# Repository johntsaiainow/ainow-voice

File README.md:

# AI-Now Voice Hardware

Open-source PCB hardware repository for **AiNow Voice S3** — a family of ESP32-S3 based dual-microphone AI voice assistant cards.

> **Note:** This hardware is no longer tied to the "XiaoZhi" firmware. It is a general-purpose ESP32-S3 voice platform compatible with any ESP-SR / ESP-ADF / custom voice pipeline.

---

## 📂 Product Variations (directly under root)

| Variation | MCU | Mic | Display | Amp | Status | Folder |
| :--- | :--- | :--- | :--- | :--- | :--- | :--- |
| **AiNow Voice S3 — Standard** | ESP32-S3-WROOM-1-N16R8 | 2× I2S MEMS (INMP441/MSM261S socketed) | ST7789 1.54" TFT | MAX98357A | Released | [`s3-dualmic-standard`](./s3-dualmic-standard) |
| AiNow Voice S3 — Mini | ESP32-S3-WROOM-1-N8R8 | 2× I2S MEMS | None (LED status only) | MAX98357A | Planned | [`s3-dualmic-mini`](./s3-dualmic-mini) |
| AiNow Voice S3 — Pro | ESP32-S3-WROOM-1-N16R8 | ES7210 4-ch ADC + Analog MEMS | ST7789 + OLED | NS4168 + passive filter | In design | [`s3-dualmic-pro`](./s3-dualmic-pro) |

> Each sub-folder contains its own `README.md`, KiCad schematic/PCB files, Gerber output, and 3D model notes.

---

## 🚀 Quick Start

1. Enter the variation folder you want to build (e.g. `s3-dualmic-standard/`) and read its `README.md`.
2. Open the `.kicad_pro` file with **KiCad 10** to view the schematic and PCB 3D model.
3. Export Gerber per the sub-folder instructions and send to the board house.

---

## 📄 License

All hardware design files in this repository are released under **CC BY 4.0** unless otherwise noted in a sub-folder.

---

**AI-Now Inc.** — 11/2026

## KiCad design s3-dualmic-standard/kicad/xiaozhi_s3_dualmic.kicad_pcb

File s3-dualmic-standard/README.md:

# AiNow Voice S3 — Standard

ESP32-S3 dual-microphone AI voice card — Standard Edition

---

## Overview

Standard Edition is the base model of the AiNow Voice S3 series, suitable for desktop assistants, voice assistant prototypes, and development boards.

## Hardware Specifications

| Item | Specification |
| :--- | :--- |
| **Main MCU** | ESP32-S3-WROOM-1-N16R8 (8 MB Octal PSRAM) |
| **Microphones** | 2× Digital I2S MEMS (INMP441 / MSM261S), socketed via 2.54mm pin headers, 54 mm center spacing |
| **Display** | ST7789 1.54" SPI TFT (240×240), socketed via 1×8 pin header |
| **Audio Output** | MAX98357A I2S Class-D amplifier, JST-PH-2P speaker connector |
| **Power** | USB Type-C (5V), TP4056 single-cell Li-ion charger, AP2112K 3.3V LDO |
| **Battery** | JST-PH-2P 3.7V Li-Po battery connector |
| **Buttons** | RST (ESP_EN) / BOOT (PTT wake) |
| **Status LED** | WS2812B RGB |
| **PCB Size** | 70 × 50 mm, rounded corners, four M3 mounting holes |
| **Layers** | 2 layers (F.Cu / B.Cu) + dual-layer GND pour |

## Folder Structure

```
s3-dualmic-standard/
├── README.md
├── kicad/
│   ├── xiaozhi_s3_dualmic.kicad_pro
│   ├── xiaozhi_s3_dualmic.kicad_sch
│   └── xiaozhi_s3_dualmic.kicad_pcb
├── gerber/           # Gerber output for board house (export and place here)
├── 3d/               # Additional STEP model references
└── docs/
    └── pinout.md     # ESP32-S3 GPIO mapping table
```

## Quick Start

1. Make sure **KiCad 10** is installed.
2. Open `kicad/xiaozhi_s3_dualmic.kicad_pro`.
3. Press `B` to fill copper zones, press `Alt + 3` to view the 3D model.
4. Use KiCad native **Push & Shove** (`X`) to complete routing following the ratsnest.
5. Export Gerber to `gerber/` and send to the manufacturer.

## GPIO Mapping (compatible with xiaozhi-esp32 firmware)

| Function | ESP32-S3 GPIO |
| :--- | :--- |
| I2S0 BCLK (Mic) | 41 |
| I2S0 WS (Mic) | 42 |
| I2S0 DIN (Mic Data) | 2 |
| I2S1 BCLK (Amp) | 15 |
| I2S1 LRCK (Amp) | 16 |
| I2S1 DOUT (Amp Data) | 7 |
| LCD SCL | 12 |
| LCD SDA | 11 |
| LCD RES | 14 |
| LCD DC | 13 |
| LCD CS | 10 |
| LCD BLK | 21 |
| RGB_DATA | 48 |
| BOOT / PTT | 0 |
| RST / ESP_EN | 3 |
| USB D- | 19 |
| USB D+ | 20 |
| VBAT_ADC | 1 |

---

**AI-Now Inc.** — 11/2026 — CC BY 4.0

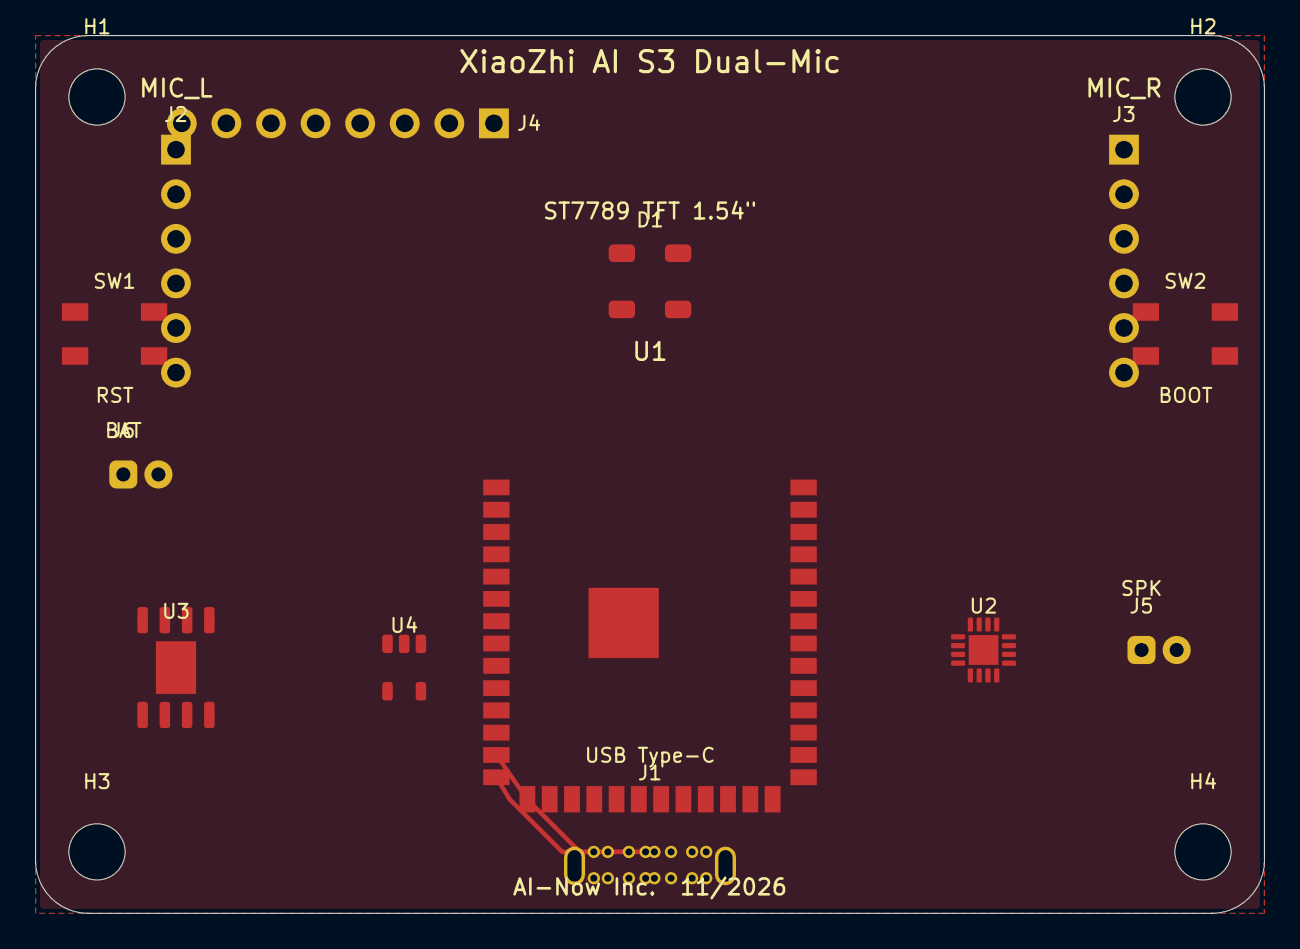
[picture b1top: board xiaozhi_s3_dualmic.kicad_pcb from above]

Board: 2 copper layers, 70.0 x 50.0 mm, 17 parts (0 on the bottom side), 23 nets.

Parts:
D1: WS2812B; LED_WS2812B_PLCC4_5.0x5.0mm_P3.2mm
H1, H2, H3, H4: M3; MountingHole_3.2mm_M3
J1: USB_Type-C; USB_C_Receptacle_GCT_USB4085
J2: MIC_L; PinHeader_1x06_P2.54mm_Vertical
J3: MIC_R; PinHeader_1x06_P2.54mm_Vertical
J4: ST7789_TFT; PinHeader_1x08_P2.54mm_Vertical
J5: Speaker; JST_PH_B2B-PH-K_1x02_P2.00mm_Vertical
J6: Battery_3.7V; JST_PH_B2B-PH-K_1x02_P2.00mm_Vertical
SW1: RST; Panasonic_EVQPUK_EVQPUB
SW2: BOOT; Panasonic_EVQPUK_EVQPUB
U1: ESP32-S3-WROOM-1-N16R8; ESP32-S3-WROOM-1
U2: MAX98357A; QFN-16-1EP_3x3mm_P0.5mm_EP1.7x1.7mm
U3: TP4056; SOIC-8-1EP_3.9x4.9mm_P1.27mm_EP2.29x3mm
U4: AP2112K-3.3; SOT-23-5

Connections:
+3.3V: D1.3, J2.2, J3.2, J3.6, J4.2, U1.2, U2.4, U4.5
+5V: J1.A4, J1.A9, J1.B4, J1.B9, U2.7, U2.8, U3.4, U3.8
ESP_BOOT: SW2.1, SW2.3, U1.27
ESP_EN: SW1.1, SW1.3, U1.3
GND: D1.4, J1.A1, J1.A12, J1.B1, J1.B12, J1.SH, J2.1, J2.6, J3.1, J4.1, J6.2, SW1.2, SW1.4, SW2.2, SW2.4, U1.1, U1.39, U1.40, U1.41, U2.2, U2.3, U2.11, U2.15, U2.17, U3.1, U3.3, U3.9, U4.2
I2S0_BCLK: J2.4, J3.4, U1.34
I2S0_DIN: J2.3, J3.3, U1.36
I2S0_WS: J2.5, J3.5, U1.35
I2S1_BCLK: U1.8, U2.16
I2S1_DOUT: U1.7, U2.1
I2S1_LRCK: U1.9, U2.14
LCD_BLK: J4.8, U1.23
LCD_CS: J4.7, U1.18
LCD_DC: J4.6, U1.21
LCD_RES: J4.5, U1.22
LCD_SCL: J4.3, U1.20
LCD_SDA: J4.4, U1.19
RGB_DATA: D1.2, U1.25
SPK+: J5.1, U2.9
SPK-: J5.2, U2.10
USB_D+: J1.A6, J1.B6, U1.14
USB_D-: J1.A7, J1.B7, U1.13
VBAT: J6.1, U3.5, U4.1, U4.3

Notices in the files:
README.md:
License: CC BY 4.0
